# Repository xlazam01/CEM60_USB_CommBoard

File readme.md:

# iOptron CEM60 USB Communication

This is a small project which enabled CEM60 mount to communicate directly over USB instead of RS232.

# Files

Schematic and PCB files in repository

## Photos

See Photos folder for final result

# Instalation

1. Remove the cover with RS232 connector
2. Disconnect two cables
3. Remove old PCB
4. Install new USB enabled PCB
5. Plug cables back
6. Reinstall board and cover
7. Have fun!!

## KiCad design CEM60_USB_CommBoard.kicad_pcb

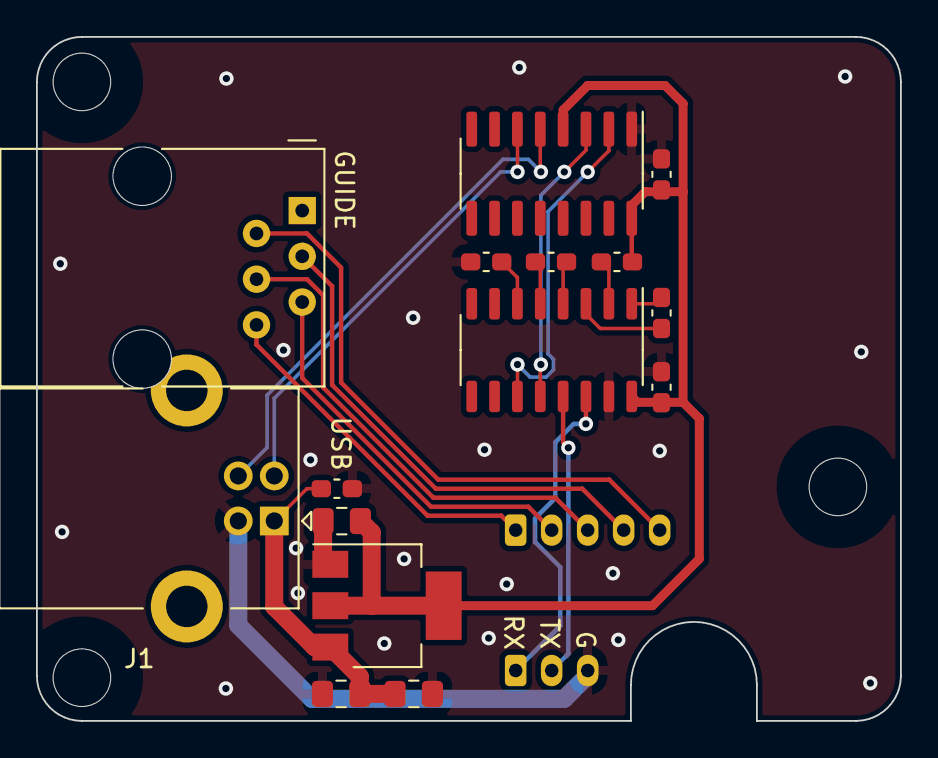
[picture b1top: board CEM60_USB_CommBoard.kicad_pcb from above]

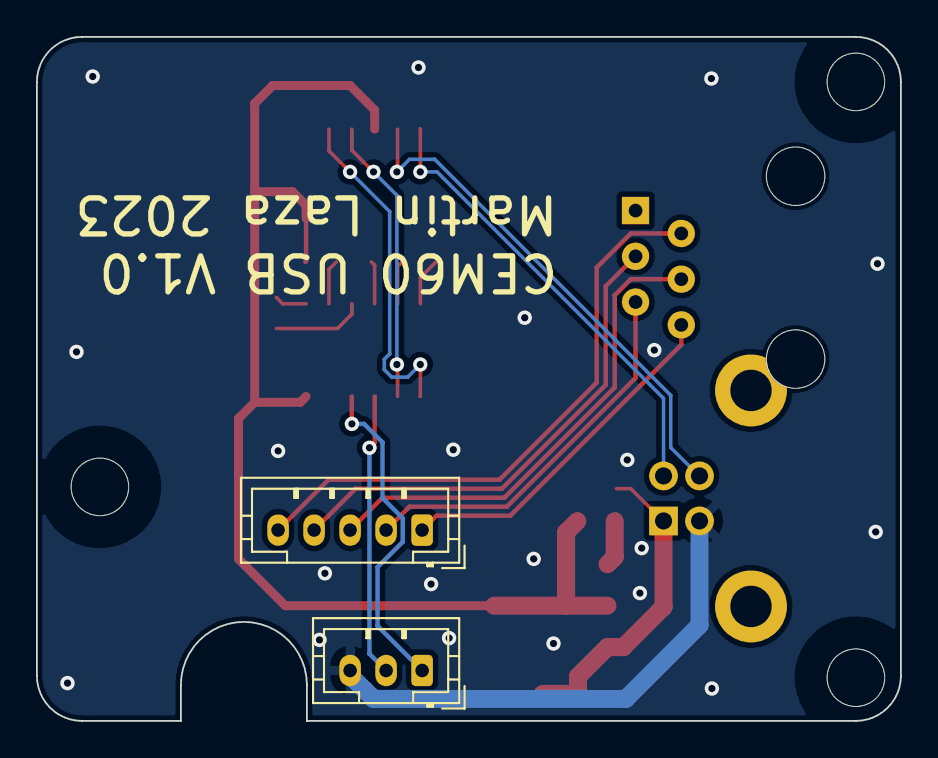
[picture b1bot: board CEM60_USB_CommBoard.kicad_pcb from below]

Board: 2 copper layers, 48.0 x 38.0 mm, 17 parts (2 on the bottom side), 20 nets.

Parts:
C1, C2, C4: 10u/25V/0805; C_0805_2012Metric_Pad1.18x1.45mm_HandSolder
C3, C5, C6, C7, C8, C9, C10: 100n/50V/0603; C_0603_1608Metric_Pad1.08x0.95mm_HandSolder
J1: USB_B; USB_B_Lumberg_2411_02_Horizontal
J2: 6P6C; RJ12_Amphenol_54601
J3: Conn_01x04; JST_PH_B3B-PH-K_1x03_P2.00mm_Vertical
J4: Conn_01x05; JST_PH_B5B-PH-K_1x05_P2.00mm_Vertical
U1: MAX3232; SO-16_3.9x9.9mm_P1.27mm
U2: CH340C; SOIC-16_3.9x9.9mm_P1.27mm
U3: AMS1117-3.3; SOT-223-3_TabPin2

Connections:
+3.3V: C4.1, C5.2, C6.2, C10.2, U1.16 (VCC), U2.4 (V3), U2.16 (VCC), U3.2 (VO)
/RX: J3.1, U1.14 (T1OUT)
/TX: J3.2, U1.13 (R1IN)
GND: C1.2, C2.2, C3.1, C4.2, C5.1, C7.2, C10.1, J1.4 (GND), J3.3, U1.15 (GND), U2.1 (GND), U3.1 (GND)
unnamed: J1.3 (D+), U2.5 (UD+)
unnamed: J1.2 (D-), U2.6 (UD-)
unnamed: J2.6, J4.1
unnamed: J2.5, J4.2
unnamed: J2.4, J4.3
unnamed: J2.3, J4.4
unnamed: J2.2, J4.5
unnamed: C9.1, U1.1 (C1+)
unnamed: C9.2, U1.3 (C1-)
unnamed: C8.1, U1.4 (C2+)
unnamed: C8.2, U1.5 (C2-)
unnamed: U1.12 (R1OUT), U2.3 (RXD)
unnamed: U1.11 (T1IN), U2.2 (TXD)
unnamed: C6.1, U1.2 (VS+)
unnamed: C7.1, U1.6 (VS-)
VBUS: C1.1, C2.1, C3.2, J1.1 (VBUS), U3.3 (VI)

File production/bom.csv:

Designator,Footprint,Quantity,Value,LCSC Part #
"C1, C2, C4",0805,3,10u/25V/0805,
"C10, C3, C5, C6, C7, C8, C9",0603,7,100n/50V/0603,
J1,USB_B_Lumberg_2411_02_Horizontal,1,USB_B,
J2,RJ12_Amphenol_54601,1,6P6C,
J3,JST_PH_B3B-PH-K_1x03_P2.00mm_Vertical,1,Conn_01x04,
J4,JST_PH_B5B-PH-K_1x05_P2.00mm_Vertical,1,Conn_01x05,
U1,SO-16_3.9x9.9mm_P1.27mm,1,MAX3232,
U2,SOIC-16_3.9x9.9mm_P1.27mm,1,CH340C,
U3,SOT-223-3_TabPin2,1,AMS1117-3.3,

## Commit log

2023-08-04 V1.0 hardware released
2023-08-04 Added photos
